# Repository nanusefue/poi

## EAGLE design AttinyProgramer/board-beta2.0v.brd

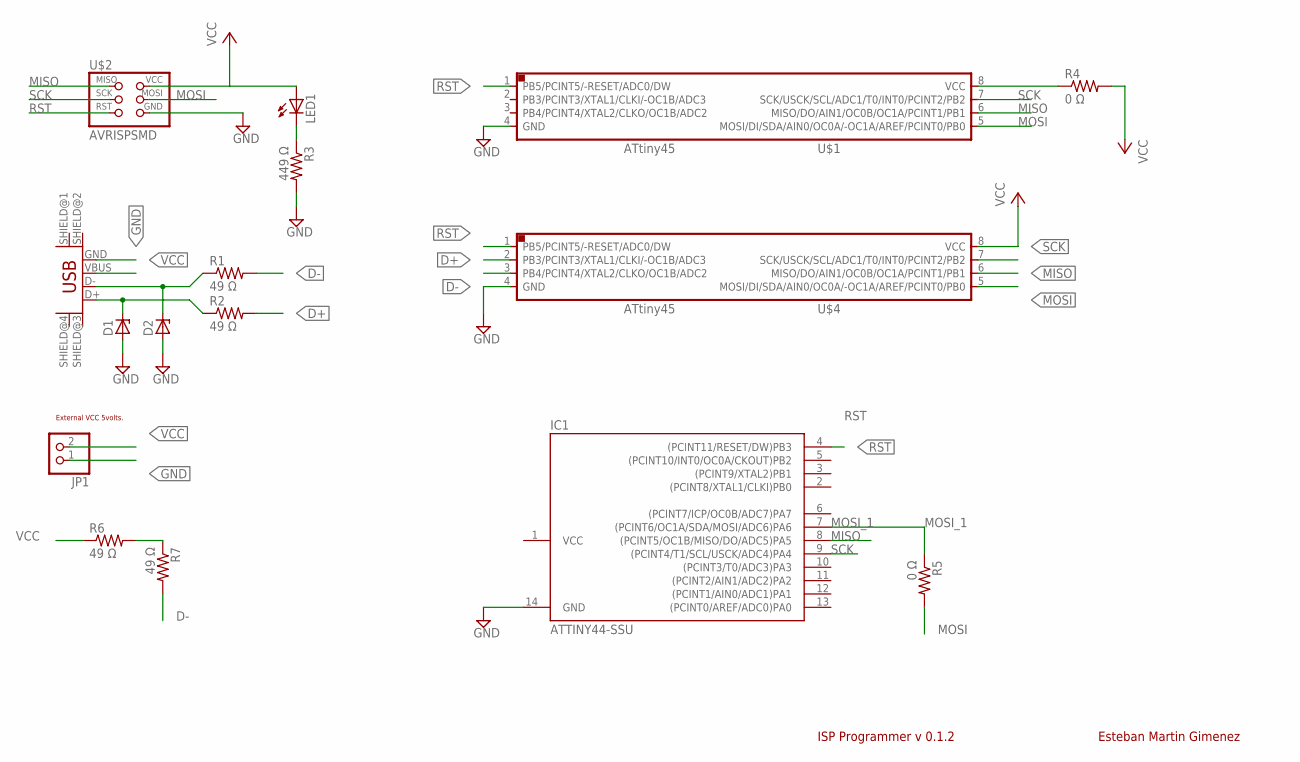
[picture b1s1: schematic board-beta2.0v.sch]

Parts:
D1, D2: ZENER_DIODESOD123; SOD123
IC1: ATTINY44-SSU; SOIC14
JP1: PINHD-1X2; 1X02
LED1: LEDCHIPLED_1206; CHIPLED_1206
R1, R2, R6, R7: 49 Ω; R1206FAB
R3: 449 Ω; R1206FAB
R4, R5: 0 Ω; R1206FAB
U$1, U$4: ATTINY45SI; SOIC8
U$2: AVRISPSMD; 2X03SMD
U$5: USB_MINIB

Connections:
D+: R2.2, U$4.2 (PB3/PCINT3/XTAL1/CLKI/-OC1B/ADC3)
D-: R1.2, R7.2, U$4.3 (PB4/PCINT4/XTAL2/CLKO/OC1B/ADC2)
GND: D1.ANODE, D2.ANODE, IC1.14 (GND), JP1.1, R3.2, U$1.4 (GND), U$2.6 (GND), U$4.4 (GND), U$5.GND
MISO: IC1.8 ((PCINT5/OC1B/MISO/DO/ADC5)PA5), U$1.6 (MISO/DO/AIN1/OC0B/OC1A/PCINT1/PB1), U$2.1 (MISO), U$4.6 (MISO/DO/AIN1/OC0B/OC1A/PCINT1/PB1)
MOSI: R5.2, U$1.5 (MOSI/DI/SDA/AIN0/OC0A/-OC1A/AREF/PCINT0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), U$2.4 (MOSI), U$4.5 (MOSI/DI/SDA/AIN0/OC0A/-OC1A/AREF/PCINT0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)
MOSI_1: IC1.7 ((PCINT6/OC1A/SDA/MOSI/ADC6)PA6), R5.1
unnamed: R4.1, U$1.8 (VCC)
unnamed: LED1.C, R3.1
unnamed: R6.2, R7.1
RST: IC1.4 ((PCINT11/RESET/DW)PB3), U$1.1 (PB5/PCINT5/-RESET/ADC0/DW), U$2.5 (RST), U$4.1 (PB5/PCINT5/-RESET/ADC0/DW)
SCK: IC1.9 ((PCINT4/T1/SCL/USCK/ADC4)PA4), U$1.7 (SCK/USCK/SCL/ADC1/T0/INT0/PCINT2/PB2), U$2.3 (SCK), U$4.7 (SCK/USCK/SCL/ADC1/T0/INT0/PCINT2/PB2)
VCC: IC1.1 (VCC), JP1.2, LED1.A, R4.2, R6.1, U$2.2 (VCC), U$5.VBUS
_D+: D1.CATHODE, R2.1, U$5.D+
_D-: D2.CATHODE, R1.1, U$5.D-

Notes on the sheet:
Esteban Martin Gimenez
ISP Programmer v 0.1.2
External VCC 5volts.

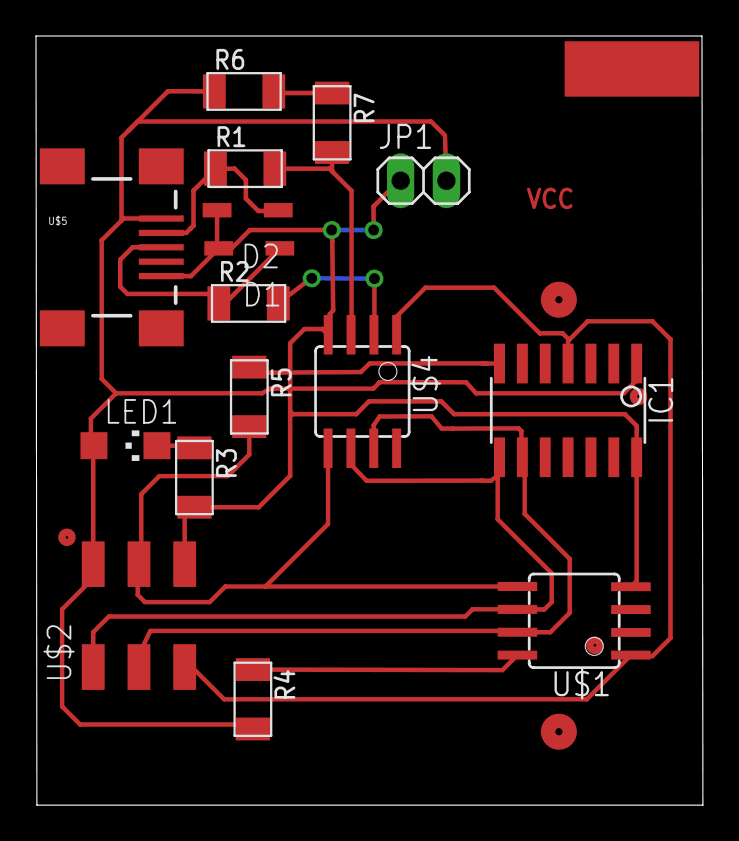
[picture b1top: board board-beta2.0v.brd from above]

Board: 2 copper layers, 37.1 x 42.7 mm, 16 parts (0 on the bottom side), 14 nets.

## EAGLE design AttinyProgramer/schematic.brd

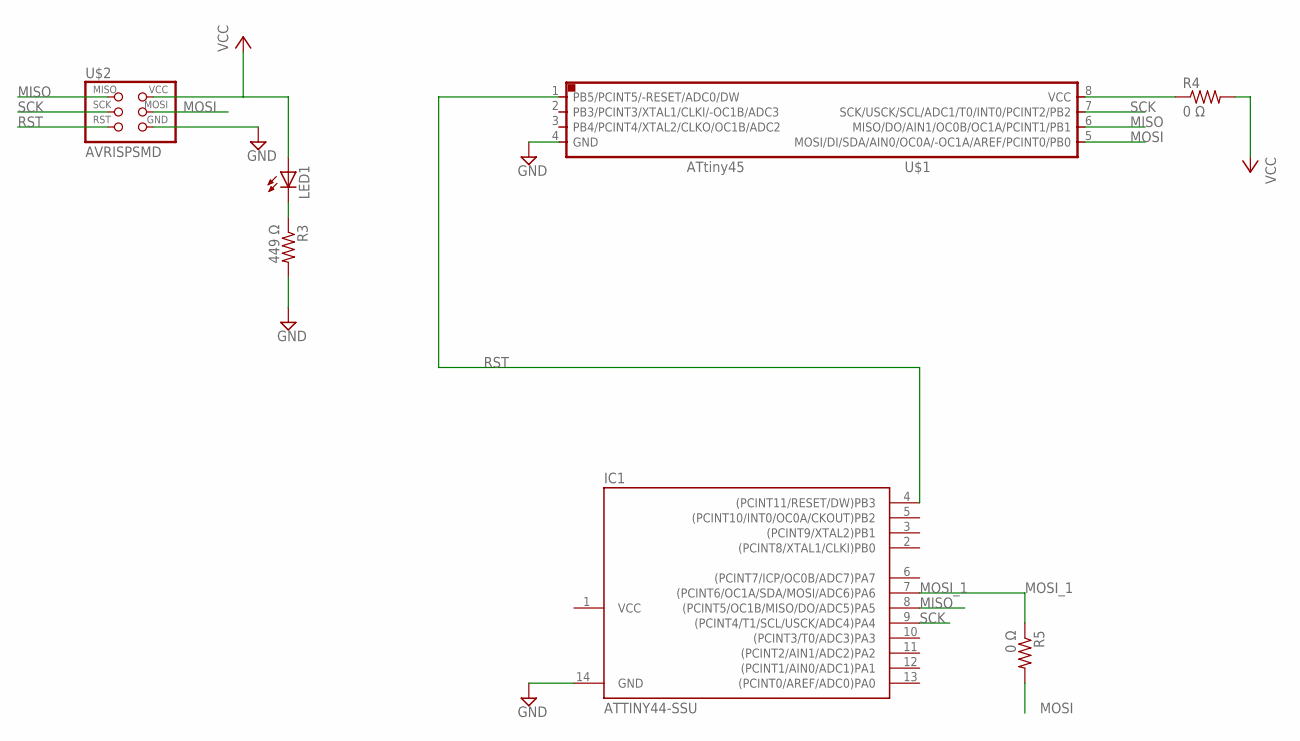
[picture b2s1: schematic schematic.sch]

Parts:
IC1: ATTINY44-SSU; SOIC14
LED1: LEDCHIPLED_1206; CHIPLED_1206
R3: 449 Ω; R1206
R4, R5: 0 Ω; R1206
U$1: ATTINY45SI; SOIC8
U$2: AVRISPSMD; 2X03SMD

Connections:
GND: IC1.14 (GND), R3.2, U$1.4 (GND), U$2.6 (GND)
MISO: IC1.8 ((PCINT5/OC1B/MISO/DO/ADC5)PA5), U$1.6 (MISO/DO/AIN1/OC0B/OC1A/PCINT1/PB1), U$2.1 (MISO)
MOSI: R5.2, U$1.5 (MOSI/DI/SDA/AIN0/OC0A/-OC1A/AREF/PCINT0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), U$2.4 (MOSI)
MOSI_1: IC1.7 ((PCINT6/OC1A/SDA/MOSI/ADC6)PA6), R5.1
unnamed: R4.1, U$1.8 (VCC)
unnamed: LED1.C, R3.1
RST: IC1.4 ((PCINT11/RESET/DW)PB3), U$1.1 (PB5/PCINT5/-RESET/ADC0/DW), U$2.5 (RST)
SCK: IC1.9 ((PCINT4/T1/SCL/USCK/ADC4)PA4), U$1.7 (SCK/USCK/SCL/ADC1/T0/INT0/PCINT2/PB2), U$2.3 (SCK)
VCC: IC1.1 (VCC), LED1.A, R4.2, U$2.2 (VCC)

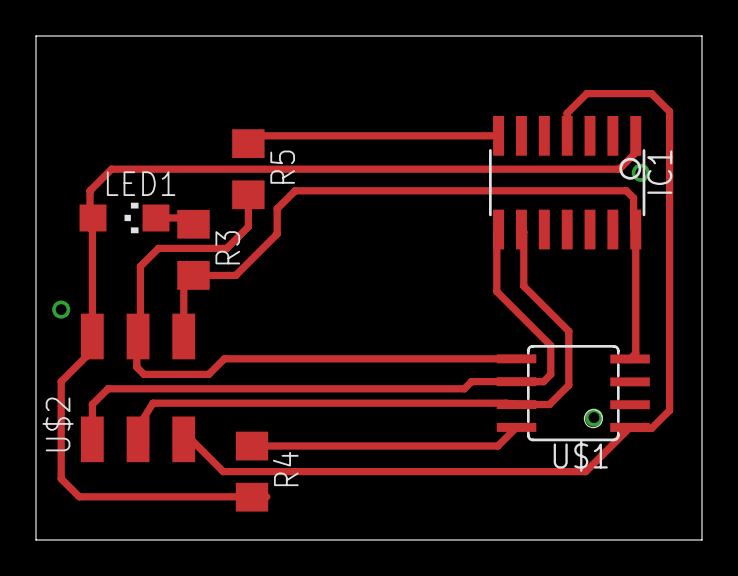
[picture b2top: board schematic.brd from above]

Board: 2 copper layers, 37.0 x 28.0 mm, 7 parts (0 on the bottom side), 9 nets.

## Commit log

2016-12-28 Set theme jekyll-theme-cayman
2016-12-29 json test
2016-12-29 fix json
2016-12-29 fix file dowload
2016-12-29 fix package name
2016-12-29 fix name
2016-12-29 fix path file
2016-12-29 v 0.0.2
2016-12-29 add custom tools micronucleus
2016-12-29 add custom tools micronucleus 2.0a5
2016-12-29 fix package name tools
2016-12-29 change name tools
2016-12-29 new version
2016-12-29 json new realease 0.0.3
2016-12-29 new version 0.0.4
2016-12-29 new realeas 0.0.5
2016-12-29 change tiny core
2016-12-29 change mmcpu
2016-12-29 add change mccpu
2016-12-29 version 0.0.8 primer version que funciona
2016-12-29 fix path tools
2016-12-31 add oxs and linux 32 bit and osx
2016-12-31 añadir other platform
2016-12-31 fix platform
2016-12-31 tool for osx
2016-12-31 tool for osx fix crc
2016-12-31 fix crc
2016-12-31 osx add crs
2016-12-31 Attiny programer pcb
2016-12-31 fix change
2016-12-31 add windows drivers
2017-01-08 add board programer bootloader
2017-04-09 clea
2017-05-01 new board
2017-05-01 change name
2017-05-01 add new version
2017-05-01 change name package
2017-05-01 fix folder
2017-05-01 fix checksum
2017-05-01 new release
